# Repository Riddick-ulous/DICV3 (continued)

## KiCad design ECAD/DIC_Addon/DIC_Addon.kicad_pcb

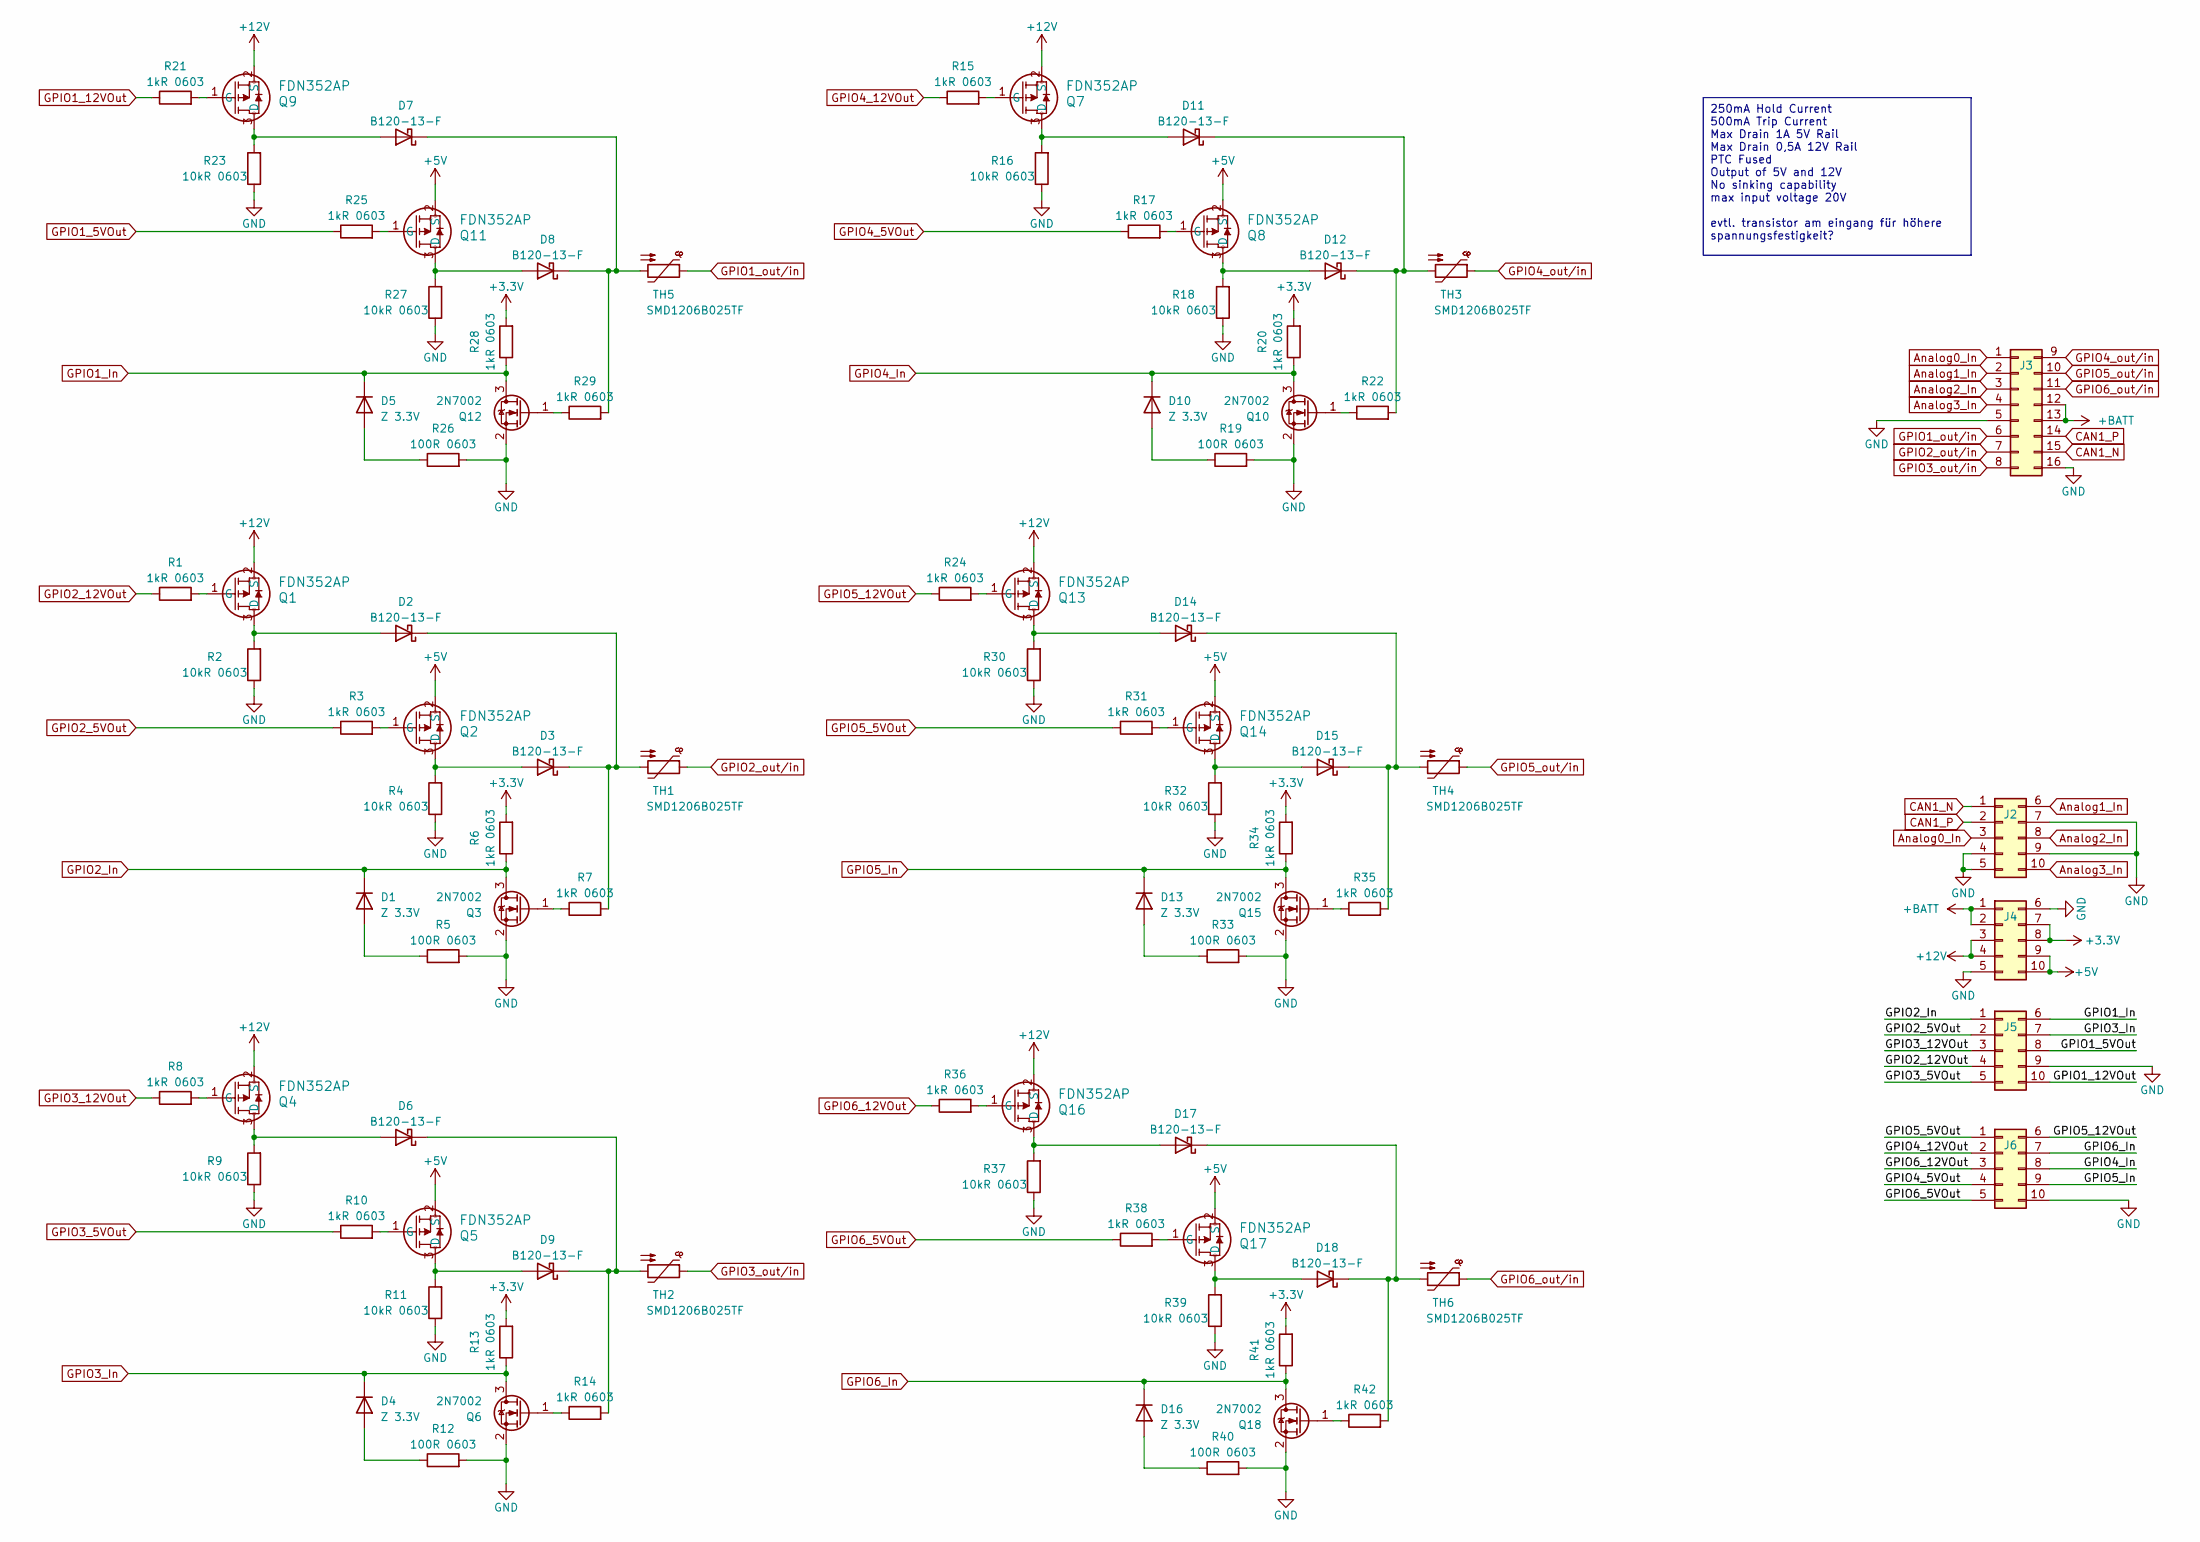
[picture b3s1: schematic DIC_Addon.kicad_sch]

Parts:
D1, D4, D5, D10, D13, D16: Z 3.3V; D_SOD-323_HandSoldering; PartNr. MM3Z3V3T1G
D2, D3, D6, D7, D8, D9, D11, D12, D14, D15, D17, D18: B120-13-F; D_SMA
J2, J4, J5, J6: Conn_02x05_Top_Bottom; PinSocket_2x05_P1.27mm_Vertical
J3: WE 62702621621; PinHeader_2x08_P1.27mm_Vertical
Q1, Q2, Q4, Q5, Q7, Q8, Q9, Q11, Q13, Q14, Q16, Q17: FDN352AP; SOT23_527AG_ONS
Q3, Q6, Q10, Q12, Q15, Q18: 2N7002; SOT-23
R1, R3, R6, R7, R8, R10, R13, R14, R15, R17, R20, R21, R22, R24, R25, R28, R29, R31, R34, R35, R36, R38, R41, R42: 1kR 0603; R_0603_1608Metric_Pad0.98x0.95mm_HandSolder
R2, R4, R9, R11, R16, R18, R23, R27, R30, R32, R37, R39: 10kR 0603; R_0603_1608Metric_Pad0.98x0.95mm_HandSolder
R5, R12, R19, R26, R33, R40: 100R 0603; R_0603_1608Metric_Pad0.98x0.95mm_HandSolder
TH1, TH2, TH3, TH4, TH5, TH6: SMD1206B025TF; R_1206_3216Metric_Pad1.30x1.75mm_HandSolder

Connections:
+3.3V: J4.7, J4.8, R6.2, R13.2, R20.2, R28.2, R34.2, R41.2
+5V: J4.9, J4.10, Q2.2 (S), Q5.2 (S), Q8.2 (S), Q11.2 (S), Q14.2 (S), Q17.2 (S)
+12V: J4.3, J4.4, Q1.2 (S), Q4.2 (S), Q7.2 (S), Q9.2 (S), Q13.2 (S), Q16.2 (S)
+BATT: J3.12, J3.13, J4.1, J4.2
Analog0_In: J2.3, J3.1
Analog1_In: J2.6, J3.2
Analog2_In: J2.8, J3.3
Analog3_In: J2.10, J3.4
CAN1_N: J2.1, J3.15
CAN1_P: J2.2, J3.14
GND: J2.4, J2.5, J2.7, J2.9, J3.5, J3.16, J4.5, J4.6, J5.9, J6.10, Q3.2 (S), Q6.2 (S), Q10.2 (S), Q12.2 (S), Q15.2 (S), Q18.2 (S), R2.1, R4.1, R5.2, R9.1, R11.1, R12.2, R16.1, R18.1, R19.2, R23.1, R26.2, R27.1, R30.1, R32.1, R33.2, R37.1, R39.1, R40.2
GPIO1_5VOut: J5.8, R25.1
GPIO1_12VOut: J5.10, R21.1
GPIO1_In: D5.1 (K), J5.6, Q12.3 (D), R28.1
GPIO1_out/in: J3.6, TH5.1
GPIO2_5VOut: J5.2, R3.1
GPIO2_12VOut: J5.4, R1.1
GPIO2_In: D1.1 (K), J5.1, Q3.3 (D), R6.1
GPIO2_out/in: J3.7, TH1.1
GPIO3_5VOut: J5.5, R10.1
GPIO3_12VOut: J5.3, R8.1
GPIO3_In: D4.1 (K), J5.7, Q6.3 (D), R13.1
GPIO3_out/in: J3.8, TH2.1
GPIO4_5VOut: J6.4, R17.1
GPIO4_12VOut: J6.2, R15.1
GPIO4_In: D10.1 (K), J6.8, Q10.3 (D), R20.1
GPIO4_out/in: J3.9, TH3.1
GPIO5_5VOut: J6.1, R31.1
GPIO5_12VOut: J6.6, R24.1
GPIO5_In: D13.1 (K), J6.9, Q15.3 (D), R34.1
GPIO5_out/in: J3.10, TH4.1
GPIO6_5VOut: J6.5, R38.1
GPIO6_12VOut: J6.3, R36.1
GPIO6_In: D16.1 (K), J6.7, Q18.3 (D), R41.1
GPIO6_out/in: J3.11, TH6.1
unnamed: D1.2 (A), R5.1
unnamed: D2.2 (A), Q1.3 (D), R2.2
unnamed: D2.1 (K), D3.1 (K), R7.2, TH1.2
unnamed: D3.2 (A), Q2.3 (D), R4.2
unnamed: D4.2 (A), R12.1
unnamed: D5.2 (A), R26.1
unnamed: D6.2 (A), Q4.3 (D), R9.2
unnamed: D6.1 (K), D9.1 (K), R14.2, TH2.2
unnamed: D7.2 (A), Q9.3 (D), R23.2
unnamed: D7.1 (K), D8.1 (K), R29.2, TH5.2
unnamed: D8.2 (A), Q11.3 (D), R27.2
unnamed: D9.2 (A), Q5.3 (D), R11.2
unnamed: D10.2 (A), R19.1
unnamed: D11.2 (A), Q7.3 (D), R16.2
unnamed: D11.1 (K), D12.1 (K), R22.2, TH3.2
unnamed: D12.2 (A), Q8.3 (D), R18.2
unnamed: D13.2 (A), R33.1
unnamed: D14.2 (A), Q13.3 (D), R30.2
unnamed: D14.1 (K), D15.1 (K), R35.2, TH4.2
unnamed: D15.2 (A), Q14.3 (D), R32.2
unnamed: D16.2 (A), R40.1
unnamed: D17.2 (A), Q16.3 (D), R37.2
unnamed: D17.1 (K), D18.1 (K), R42.2, TH6.2
unnamed: D18.2 (A), Q17.3 (D), R39.2
unnamed: Q1.1 (G), R1.2
unnamed: Q2.1 (G), R3.2
unnamed: Q3.1 (G), R7.1
unnamed: Q4.1 (G), R8.2
unnamed: Q5.1 (G), R10.2
unnamed: Q6.1 (G), R14.1
unnamed: Q7.1 (G), R15.2
unnamed: Q8.1 (G), R17.2
unnamed: Q9.1 (G), R21.2
unnamed: Q10.1 (G), R22.1
unnamed: Q11.1 (G), R25.2
unnamed: Q12.1 (G), R29.1
unnamed: Q13.1 (G), R24.2
unnamed: Q14.1 (G), R31.2
unnamed: Q15.1 (G), R35.1
unnamed: Q16.1 (G), R36.2
unnamed: Q17.1 (G), R38.2
unnamed: Q18.1 (G), R42.1

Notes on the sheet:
250mA Hold Current 500mA Trip Current Max Drain 1A 5V Rail Max Drain 0,5A 12V Rail PTC Fused Output of 5V and 12V No sinking capability max input voltage 20V evtl. transistor am eingang für höhere spannungsfestigkeit?

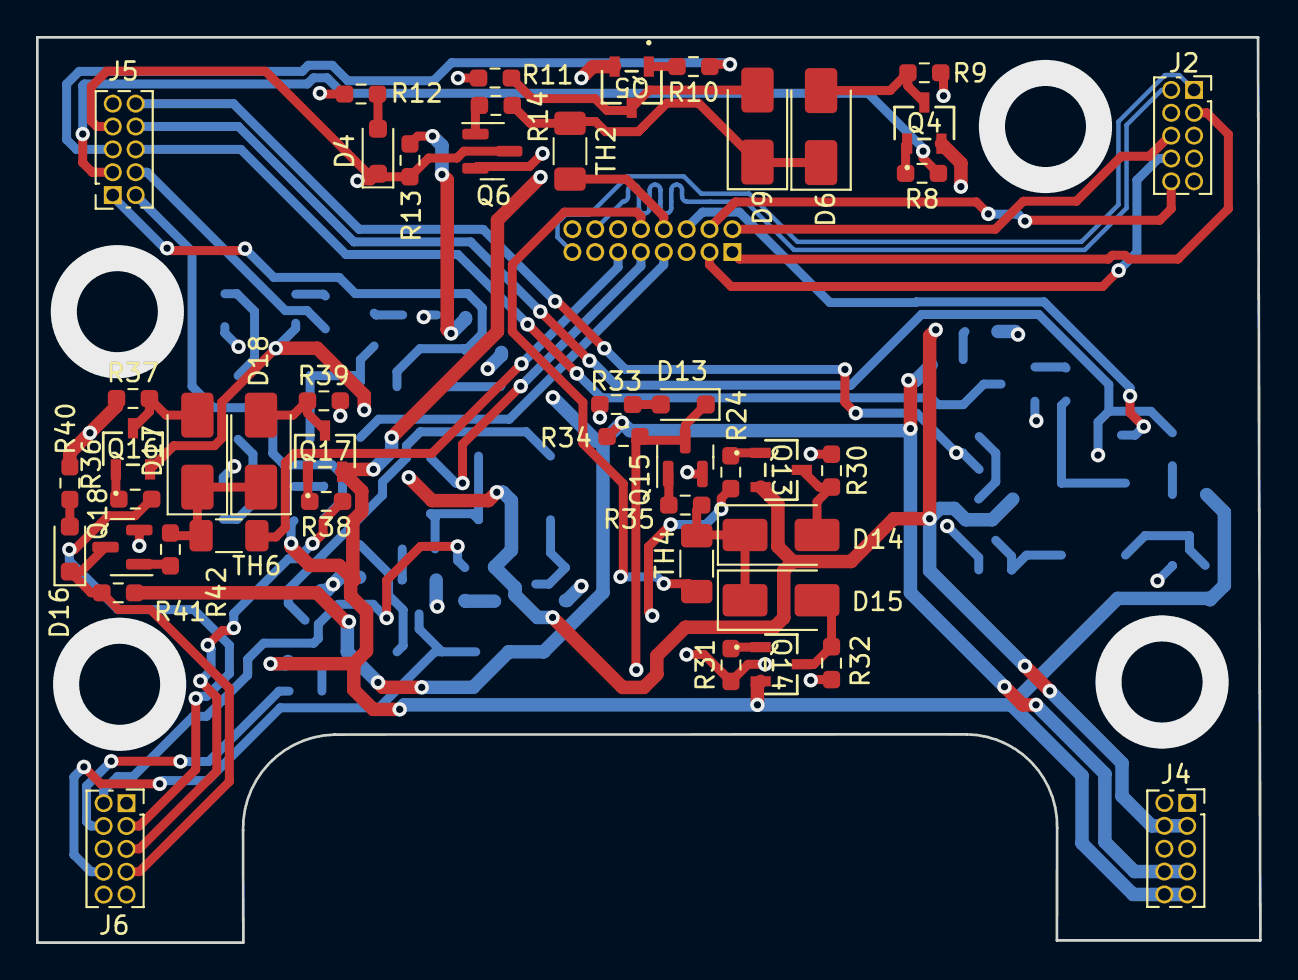
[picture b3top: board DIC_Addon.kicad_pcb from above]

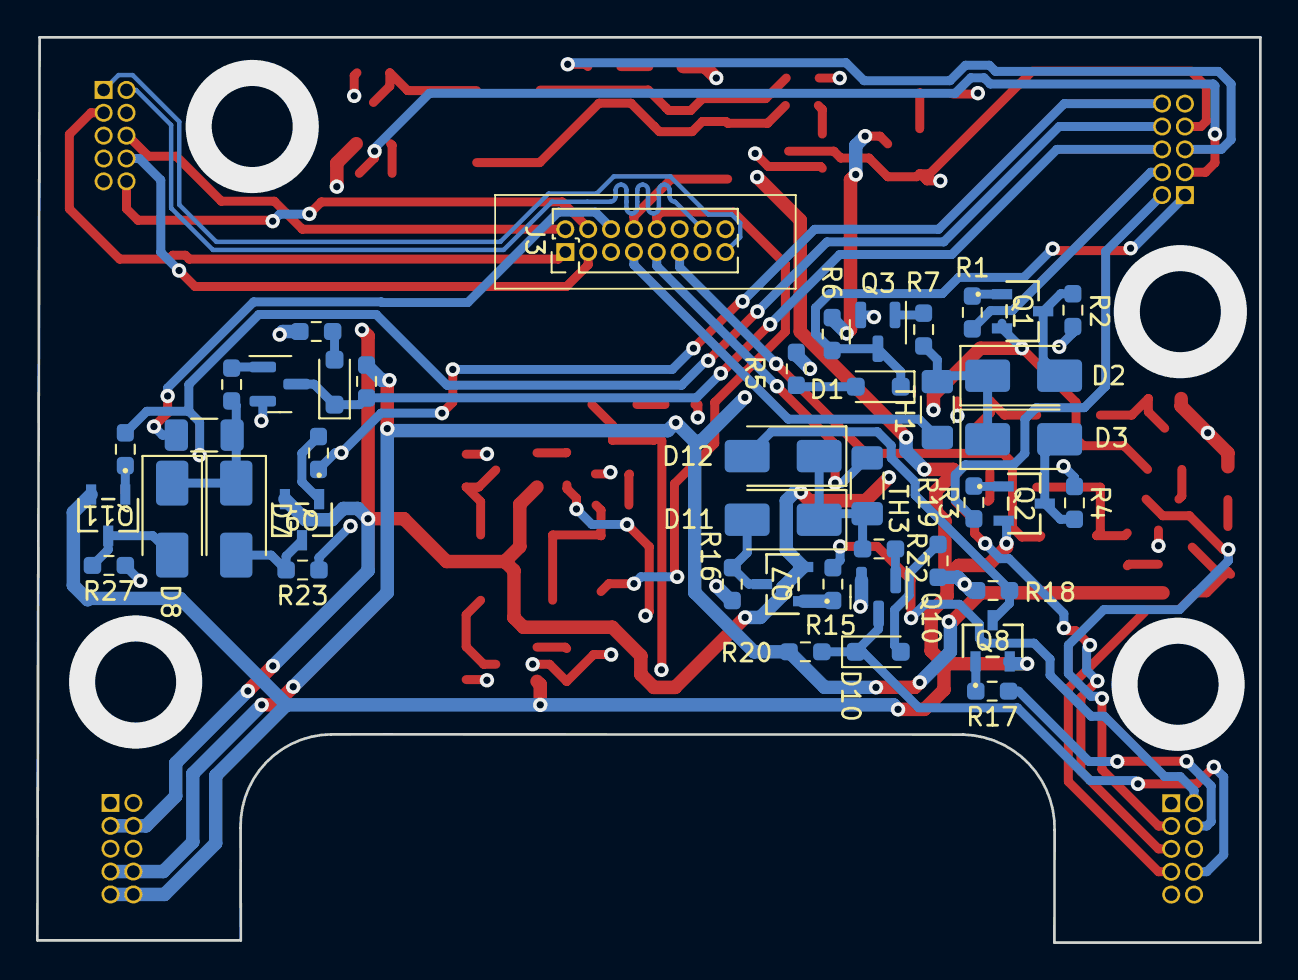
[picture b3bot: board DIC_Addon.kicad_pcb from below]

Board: 4 copper layers, 67.9 x 50.3 mm, 89 parts (43 on the bottom side), 77 nets.

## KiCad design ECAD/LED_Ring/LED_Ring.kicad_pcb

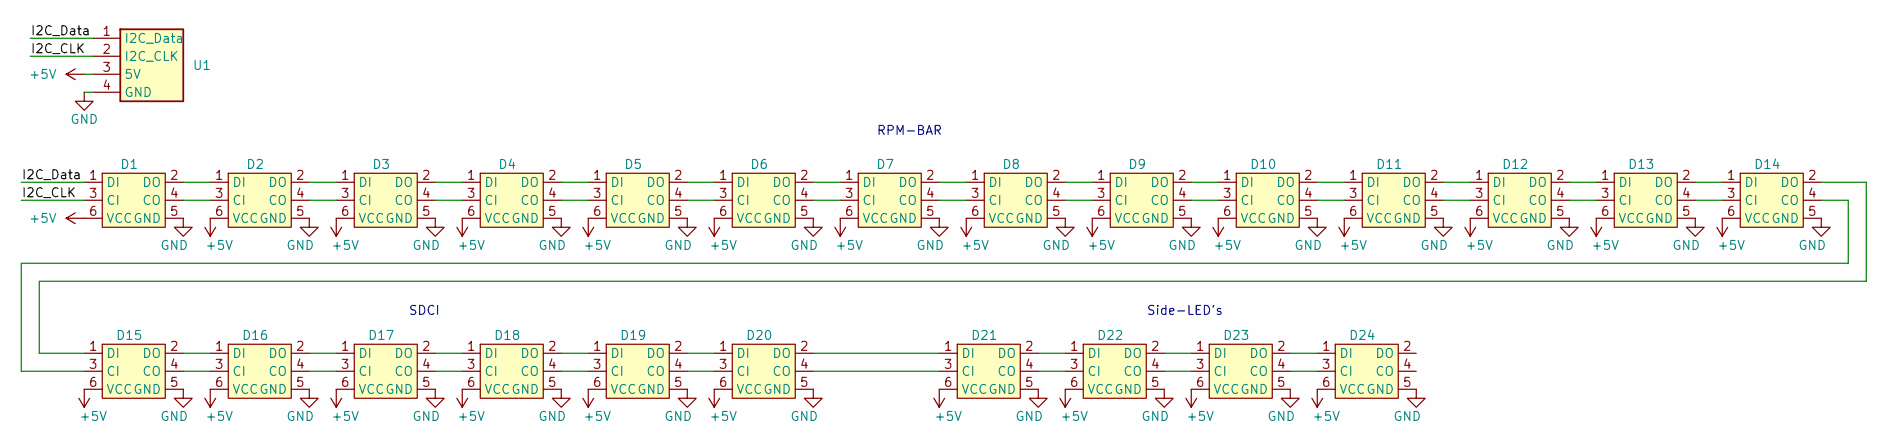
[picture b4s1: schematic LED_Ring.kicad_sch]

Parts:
D1, D2, D3, D4, D5, D6, D7, D8, D9, D10, D11, D12, D13, D14, D15, D16, D17, D18, D19, D20, D21, D22, D23, D24: BB-2020BGR-TRB
U1: LED_Ring

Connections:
+5V: D1.6 (VCC), D2.6 (VCC), D3.6 (VCC), D4.6 (VCC), D5.6 (VCC), D6.6 (VCC), D7.6 (VCC), D8.6 (VCC), D9.6 (VCC), D10.6 (VCC), D11.6 (VCC), D12.6 (VCC), D13.6 (VCC), D14.6 (VCC), D15.6 (VCC), D16.6 (VCC), D17.6 (VCC), D18.6 (VCC), D19.6 (VCC), D20.6 (VCC), D21.6 (VCC), D22.6 (VCC), D23.6 (VCC), D24.6 (VCC), U1.3 (5V)
/I2C_CLK: D1.3 (CI), U1.2 (I2C_CLK)
/I2C_Data: D1.1 (DI), U1.1 (I2C_Data)
GND: D1.5 (GND), D2.5 (GND), D3.5 (GND), D4.5 (GND), D5.5 (GND), D6.5 (GND), D7.5 (GND), D8.5 (GND), D9.5 (GND), D10.5 (GND), D11.5 (GND), D12.5 (GND), D13.5 (GND), D14.5 (GND), D15.5 (GND), D16.5 (GND), D17.5 (GND), D18.5 (GND), D19.5 (GND), D20.5 (GND), D21.5 (GND), D22.5 (GND), D23.5 (GND), D24.5 (GND), U1.4 (GND)
unnamed: D1.4 (CO), D2.3 (CI)
unnamed: D1.2 (DO), D2.1 (DI)
unnamed: D2.4 (CO), D3.3 (CI)
unnamed: D2.2 (DO), D3.1 (DI)
unnamed: D3.4 (CO), D4.3 (CI)
unnamed: D3.2 (DO), D4.1 (DI)
unnamed: D4.4 (CO), D5.3 (CI)
unnamed: D4.2 (DO), D5.1 (DI)
unnamed: D5.4 (CO), D6.3 (CI)
unnamed: D5.2 (DO), D6.1 (DI)
unnamed: D6.4 (CO), D7.3 (CI)
unnamed: D6.2 (DO), D7.1 (DI)
unnamed: D7.4 (CO), D8.3 (CI)
unnamed: D7.2 (DO), D8.1 (DI)
unnamed: D8.4 (CO), D9.3 (CI)
unnamed: D8.2 (DO), D9.1 (DI)
unnamed: D9.4 (CO), D10.3 (CI)
unnamed: D10.4 (CO), D11.3 (CI)
unnamed: D9.2 (DO), D10.1 (DI)
unnamed: D10.2 (DO), D11.1 (DI)
unnamed: D11.4 (CO), D12.3 (CI)
unnamed: D11.2 (DO), D12.1 (DI)
unnamed: D12.4 (CO), D13.3 (CI)
unnamed: D12.2 (DO), D13.1 (DI)
unnamed: D13.4 (CO), D14.3 (CI)
unnamed: D13.2 (DO), D14.1 (DI)
unnamed: D14.4 (CO), D15.3 (CI)
unnamed: D14.2 (DO), D15.1 (DI)
unnamed: D15.4 (CO), D16.3 (CI)
unnamed: D15.2 (DO), D16.1 (DI)
unnamed: D16.4 (CO), D17.3 (CI)
unnamed: D16.2 (DO), D17.1 (DI)
unnamed: D17.4 (CO), D18.3 (CI)
unnamed: D17.2 (DO), D18.1 (DI)
unnamed: D18.4 (CO), D19.3 (CI)
unnamed: D18.2 (DO), D19.1 (DI)
unnamed: D19.4 (CO), D20.3 (CI)
unnamed: D19.2 (DO), D20.1 (DI)
unnamed: D20.4 (CO), D21.3 (CI)
unnamed: D20.2 (DO), D21.1 (DI)
unnamed: D21.4 (CO), D22.3 (CI)
unnamed: D21.2 (DO), D22.1 (DI)
unnamed: D22.4 (CO), D23.3 (CI)
unnamed: D22.2 (DO), D23.1 (DI)
unnamed: D23.4 (CO), D24.3 (CI)
unnamed: D23.2 (DO), D24.1 (DI)

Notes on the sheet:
Side-LED's
SDCI
RPM-BAR

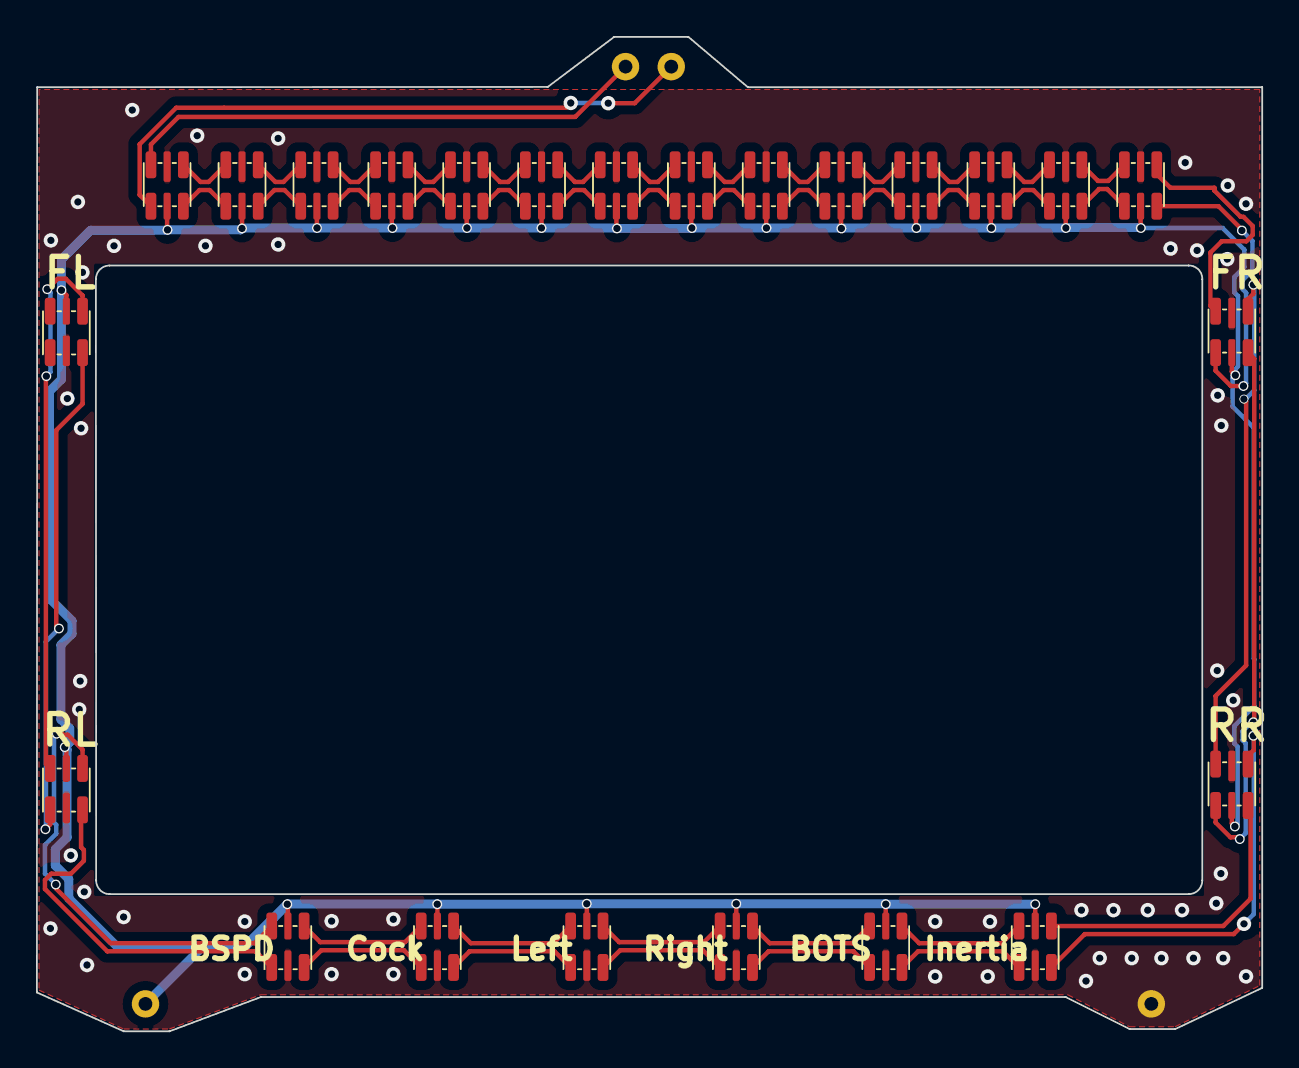
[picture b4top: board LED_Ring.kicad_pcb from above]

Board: 2 copper layers, 68.1 x 55.2 mm, 25 parts (0 on the bottom side), 50 nets.

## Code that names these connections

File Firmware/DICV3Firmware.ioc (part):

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Mcu.Name=STM32F072R(8-B)Tx
Mcu.Package=LQFP64
Mcu.UserName=STM32F072RBTx
PA0.Mode=IN0
PA0.Signal=ADC_IN0
PA1.Mode=IN1
PA1.Signal=ADC_IN1
PA10.GPIOParameters=GPIO_Label
PA10.GPIO_Label=GPIO1_12VOut
PA10.Signal=GPIO_Output
PA11.Mode=CAN_Activate
PA11.Signal=CAN_RX
PA12.Mode=CAN_Activate
PA12.Signal=CAN_TX
PA13.Mode=Serial_Wire
PA13.Signal=SYS_SWDIO
PA14.Mode=Serial_Wire
PA14.Signal=SYS_SWCLK
PA2.Mode=IN2
PA2.Signal=ADC_IN2
PA3.Mode=IN3
PA3.Signal=ADC_IN3
PA4.GPIOParameters=GPIO_Speed,GPIO_Label
PA4.GPIO_Label=nCS_Display
PA4.GPIO_Speed=GPIO_SPEED_FREQ_HIGH
PA4.Signal=GPIO_Output
PA5.GPIOParameters=GPIO_Label
PA5.GPIO_Label=SPI1_SCK_Display
PA5.Mode=TX_Only_Simplex_Unidirect_Master
PA5.Signal=SPI1_SCK
PA6.GPIOParameters=GPIO_Speed,GPIO_Label
PA6.GPIO_Label=D_nC_Display
PA6.GPIO_Speed=GPIO_SPEED_FREQ_HIGH
PA6.Signal=GPIO_Output
PA7.GPIOParameters=GPIO_Label
PA7.GPIO_Label=SPI1_MOSI_Display
PA7.Mode=TX_Only_Simplex_Unidirect_Master
PA7.Signal=SPI1_MOSI
PA8.GPIOParameters=GPIO_Label
PA8.GPIO_Label=GPIO1_In
PA8.Signal=GPIO_Input
PA9.GPIOParameters=GPIO_Label
PA9.GPIO_Label=GPIO1_5VOut
PA9.Signal=GPIO_Output
PB0.GPIOParameters=GPIO_Label
PB0.GPIO_Label=ADC2_NTC_CTRL
PB0.Signal=GPIO_Output
PB1.GPIOParameters=GPIO_Label
PB1.GPIO_Label=ADC1_NTC_CTRL
PB1.Signal=GPIO_Output
PB10.GPIOParameters=GPIO_Speed,GPIO_Label
PB10.GPIO_Label=SPI2_SCK_RGBLED
PB10.GPIO_Speed=GPIO_SPEED_FREQ_LOW
PB10.Mode=TX_Only_Simplex_Unidirect_Master
PB10.Signal=SPI2_SCK
PB11.GPIOParameters=GPIO_Label
PB11.GPIO_Label=ADC1_CTRL
PB11.Signal=GPIO_Output
PB12.GPIOParameters=GPIO_Label
PB12.GPIO_Label=ADC2_CTRL
PB12.Signal=GPIO_Output
PB13.GPIOParameters=GPIO_Label
PB13.GPIO_Label=ADC3_CTRL
PB13.Signal=GPIO_Output
PB14.GPIOParameters=GPIO_Label
PB14.GPIO_Label=GPIO3_In
PB14.Signal=GPIO_Input
PB15.GPIOParameters=GPIO_Label
PB15.GPIO_Label=GPIO3_5VOut
PB15.Signal=GPIO_Output
PB2.GPIOParameters=GPIO_Label
PB2.GPIO_Label=ADC0_NTC_CTRL
PB2.Signal=GPIO_Output
PB3.GPIOParameters=GPIO_Label
PB3.GPIO_Label=GPIO5_5VOut
PB3.Signal=GPIO_Output
PB4.GPIOParameters=GPIO_Label
PB4.GPIO_Label=GPIO5_12VOut
PB4.Signal=GPIO_Output
PB5.GPIOParameters=GPIO_Label
PB5.GPIO_Label=GPIO4_In
PB5.Signal=GPIO_Input
PB6.GPIOParameters=GPIO_Label
PB6.GPIO_Label=GPIO4_5VOut
PB6.Signal=GPIO_Output
PB7.GPIOParameters=GPIO_Label
PB7.GPIO_Label=GPIO4_12VOut
PB7.Signal=GPIO_Output
PB8.GPIOParameters=GPIO_Label
PB8.GPIO_Label=ADC3_NTC_CTRL
PB8.Signal=GPIO_Output
PB9.GPIOParameters=GPIO_Label
PB9.GPIO_Label=ADC0_CTRL
PB9.Signal=GPIO_Output
PC0.GPIOParameters=GPIO_Label
PC0.GPIO_Label=Heart
PC0.Signal=GPIO_Output
PC1.GPIOParameters=GPIO_Label
PC1.GPIO_Label=Error
PC1.Signal=GPIO_Output
PC10.GPIOParameters=GPIO_Label
PC10.GPIO_Label=GPIO6_In
PC10.Signal=GPIO_Input
PC11.GPIOParameters=GPIO_Label
PC11.GPIO_Label=GPIO6_5VOut
PC11.Signal=GPIO_Output
PC12.GPIOParameters=GPIO_Label
PC12.GPIO_Label=GPIO6_12VOut
PC12.Signal=GPIO_Output
PC3.GPIOParameters=GPIO_Speed,GPIO_Label
PC3.GPIO_Label=SPI2_MOSI_RGBLED
PC3.GPIO_Speed=GPIO_SPEED_FREQ_LOW
PC3.Mode=TX_Only_Simplex_Unidirect_Master
PC3.Signal=SPI2_MOSI
PC4.GPIOParameters=GPIO_Speed,GPIO_Label
PC4.GPIO_Label=nRES_Display
PC4.GPIO_Speed=GPIO_SPEED_FREQ_HIGH
PC4.Signal=GPIO_Output
PC6.GPIOParameters=GPIO_Label
PC6.GPIO_Label=GPIO3_12VOut
PC6.Signal=GPIO_Output
PC7.GPIOParameters=GPIO_Label
PC7.GPIO_Label=GPIO2_In
PC7.Signal=GPIO_Input
PC8.GPIOParameters=GPIO_Label
PC8.GPIO_Label=GPIO2_5VOut
PC8.Signal=GPIO_Output
PC9.GPIOParameters=GPIO_Label
PC9.GPIO_Label=GPIO2_12VOut
PC9.Signal=GPIO_Output
PD2.GPIOParameters=GPIO_Label
PD2.GPIO_Label=GPIO5_In
PD2.Signal=GPIO_Input
PF0-OSC_IN.Mode=HSE-External-Oscillator
PF0-OSC_IN.Signal=RCC_OSC_IN
PF1-OSC_OUT.Mode=HSE-External-Oscillator
PF1-OSC_OUT.Signal=RCC_OSC_OUT
RCC.HSE_VALUE=16000000
RCC.SYSCLKFreq_VALUE=48000000
RCC.SYSCLKSource=RCC_SYSCLKSOURCE_PLLCLK
board=custom

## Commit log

2025-02-17 initial commit for baseline PCB and Firmware, WIP
2025-02-18 Finish Schematic for V3 PCB
2025-03-22 switch to ribbon cable pcb interconnect
2025-03-25 finisjed PCB projekt
2025-04-17 few small changes
2025-06-22 production ready
2025-08-10 bunch o SW
    added all baseline code for Display LED, ADC etc.
2025-08-10 Muuch SW
    implemted LED via CAN
    ADC config + via can
2025-08-11 DisplayFun
    implement display functions, need to be tested aswell as ADC code
2025-08-12 boot logo implemented
